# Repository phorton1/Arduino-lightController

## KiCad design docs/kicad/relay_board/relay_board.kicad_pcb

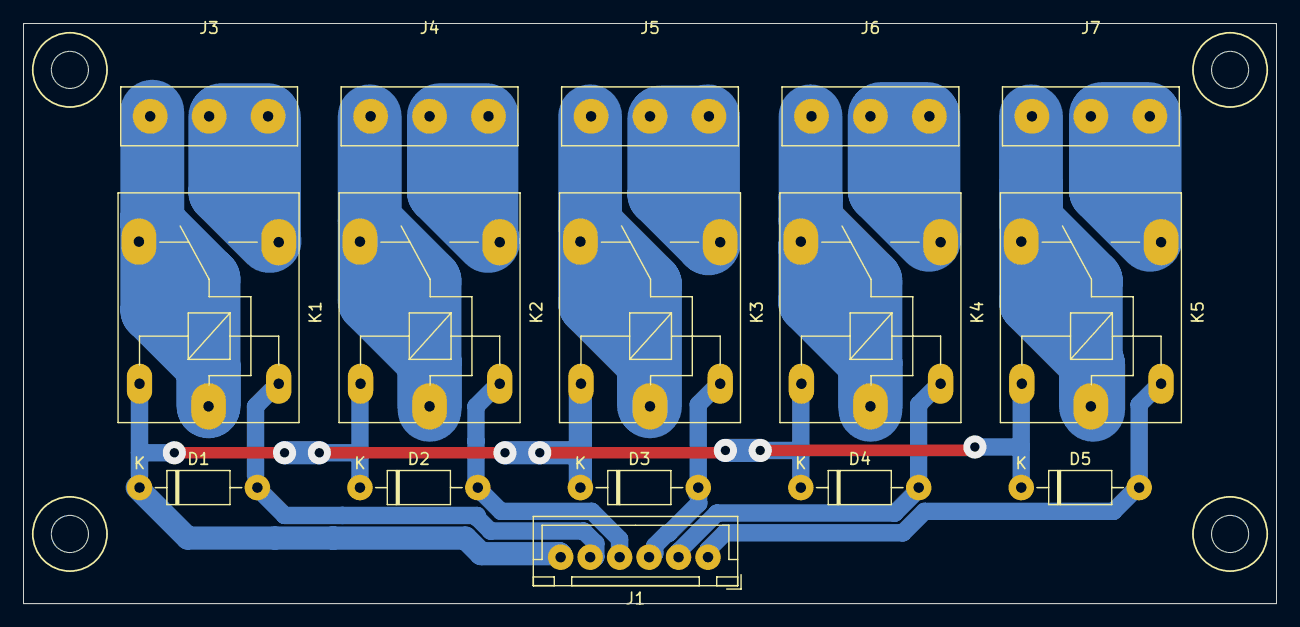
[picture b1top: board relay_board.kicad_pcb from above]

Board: 2 copper layers, 108.0 x 50.0 mm, 16 parts (0 on the bottom side), 16 nets.

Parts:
D1, D2, D3, D4, D5: 1N4001; D_DO-41_SOD81_P10.16mm_Horizontal
J1: RELAYS; myJSTx06
J3: CONN1; Phoenix5.08x3
J4: CONN2; Phoenix5.08x3
J5: CONN3; Phoenix5.08x3
J6: CONN4; Phoenix5.08x3
J7: CONN5; Phoenix5.08x3
K1, K2, K3, K4, K5: myRelay; myRelay2

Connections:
+5V: D1.1, D2.1, D3.1, D4.1, D5.1, J1.6, K1.1, K2.1, K3.1, K4.1, K5.1
unnamed: J3.1, K1.3, K1.4
unnamed: J3.2, J3.3, K1.5
unnamed: J4.1, K2.3, K2.4
unnamed: J4.2, J4.3, K2.5
unnamed: J5.1, K3.3, K3.4
unnamed: J5.2, J5.3, K3.5
unnamed: J6.1, K4.3, K4.4
unnamed: J6.2, J6.3, K4.5
unnamed: J7.1, K5.3, K5.4
unnamed: J7.2, J7.3, K5.5
RELAY1: D1.2, J1.5, K1.2
RELAY2: D2.2, J1.4, K2.2
RELAY3: D3.2, J1.3, K3.2
RELAY4: D4.2, J1.2, K4.2
RELAY5: D5.2, J1.1, K5.2

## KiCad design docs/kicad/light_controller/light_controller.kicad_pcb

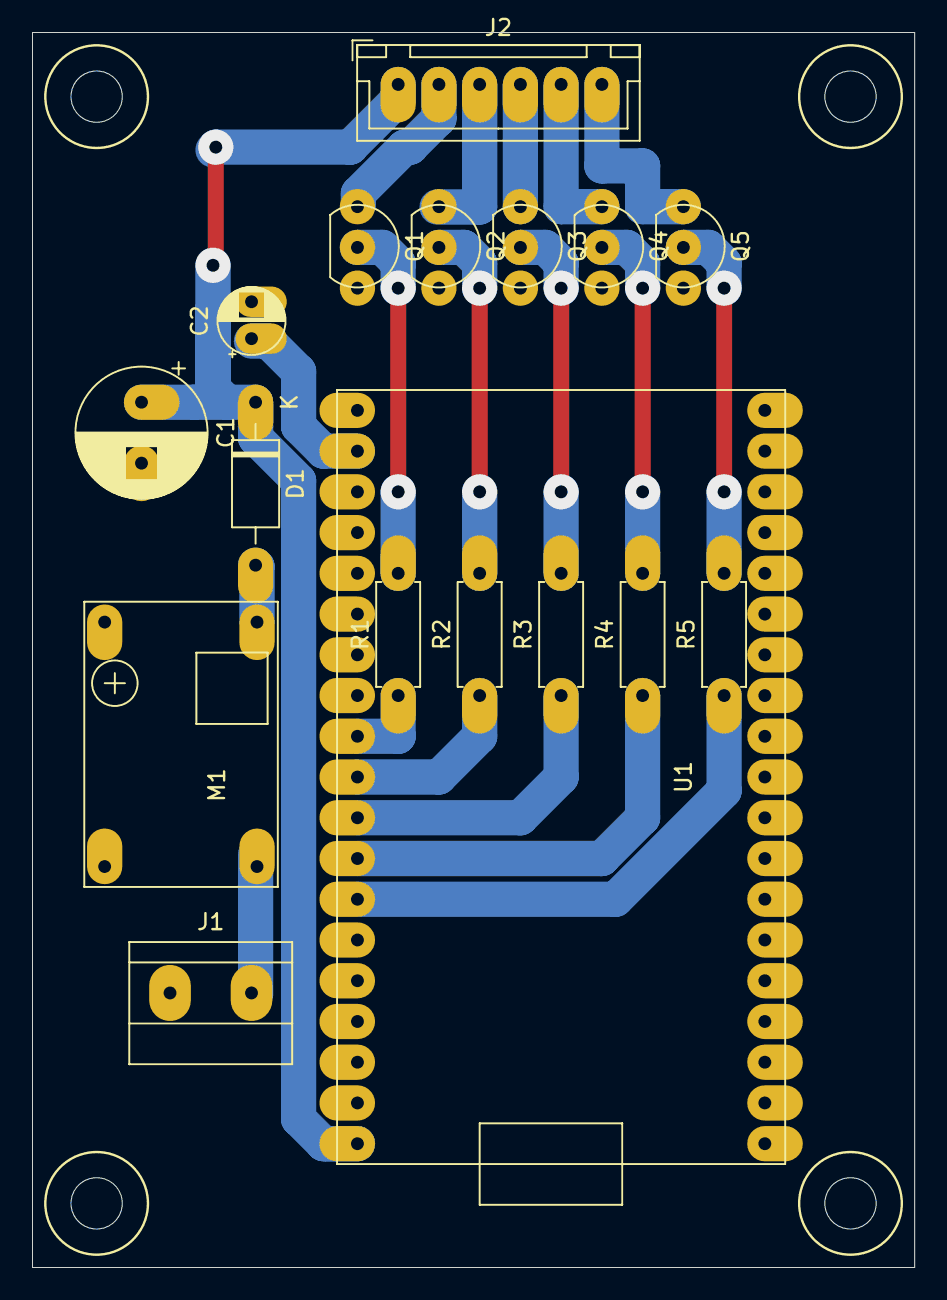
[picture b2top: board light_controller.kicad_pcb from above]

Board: 2 copper layers, 55.0 x 77.0 mm, 17 parts (0 on the bottom side), 20 nets.

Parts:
C1: 100uf; CP_my100uf
C2: 4.7uf; CP_my10uf
D1: 1N4001; D_DO-41_SOD81_P10.16mm_Horizontal
J1: POWER; myTerminalBlock_5.08x02
J2: Conn_01x06; myJSTx06
M1: BUCK01; buck-mini360
Q1, Q2, Q3, Q4, Q5: BC549; myTransistor
R1, R2, R3, R4, R5: 1K; resistor
U1: ESP32_DEV; esp32_dev

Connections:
+5V: C1.1, D1.1, J2.1, U1.1
CONTROL1: R1.1, U1.11
CONTROL2: R2.1, U1.10
CONTROL3: R3.1, U1.9
CONTROL4: R4.1, U1.8
CONTROL5: R5.1, U1.7
GND: C1.2, C2.2, J1.1, M1.1, M1.2, Q1.3, Q2.3, Q3.3, Q4.3, Q5.3, U1.6, U1.20, U1.26
unnamed: C2.1, U1.18
unnamed: D1.2, M1.3
unnamed: J1.2, M1.4
unnamed: Q1.2, R1.2
unnamed: Q2.2, R2.2
unnamed: Q3.2, R3.2
unnamed: Q4.2, R4.2
unnamed: Q5.2, R5.2
RELAY1: J2.2, Q1.1
RELAY2: J2.3, Q2.1
RELAY3: J2.4, Q3.1
RELAY4: J2.5, Q4.1
RELAY5: J2.6, Q5.1

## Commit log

2025-07-01 added Arduino-lightController repo
2025-07-10 Create relay and light controller PCB's; test
2025-07-29 added potential water level monitoring schematic to light controller
2025-12-15 submodule(data) auto_commit(b649fc3a) iotChart.js - added scheme for setting device specific series colors
2025-12-18 submodule(data) auto_commit(1adaeb45) reworked iotChart.js incremental update scheme starting with Arduino-boat-drainPump
2025-12-18 submodule(data) auto_commit(b6ac0c88) starting in Arduino-boat-arirco, major rework of iotChart.js and how charts are implemented - use common chart.html instead of specific/extra_data/device_chart.h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
2025-12-18 submodule(data) auto_commit(1efc7b72) rework iotChart.js::determineNumberTicks() starting with drain_pump
2025-12-18 submodule(data) auto_commit(78894e93) change onChartResize() to use create_chart() instead of built in jqplot.replot()
2025-12-18 submodule(data) auto_commit(40916b0c) separate iotChart.js doChart() as init only method from onXXX() UI methods - yet another rework of iotChart.js and myIOTDataLog starting with fridgeController
2025-12-18 submodule(data) auto_commit(b923e44d) back to static html for chart.html; got rid of myIOTDataLog::getChartHtml() starting with tempController
2025-12-18 submodule(data) auto_commit(a4e2ed81) change chart.html and iotChart.js to use and remove style "degree_hidden" for devices that chart things with degrees
2025-12-18 submodule(data) auto_commit(a9754dbc) fixed renamed control _degree_type
2025-12-18 submodule(data) auto_commit(03555741) fix malformed chart.html <select id='_chart_period'> text
2025-12-19 submodule(data) auto_commit(1cb3d61a) add onChartResize() back to chart.html
2025-12-19 submodule(data) auto_commit(253976a9) more changes to iotChart.js starting with tempController so at least refresh works *well* if no zooming involved
2025-12-19 commit parents
2025-12-20 submodule(data) auto_commit(eccd1fcc) iotChart.js - added save/restore of series visibility and refactored code
2025-12-31 submodule(data) auto_commit(2a8db875) add degree_type to myIOT chart_header for use in initializing iotChart.js
2026-02-22 submodule(data) auto_commit(37a6a76c) added framework for chart.html to pass "data_name" to allow multiple charts per device; ALSO store most recent chart period in browser storage
2026-03-04 submodule(data) auto_commit(75bcbcb5) iotChart.js - added smaller (UINT8, CENTIGRADE8, UINT8x10) iotDataLog LOG_TYPES and updated client ctors
2026-03-04 submodule(data) auto_commit(d6f02205) added myIotTempSensor "raw" accessors & used to shrink fridgeController.dataLog file size; got rid of FAKE_COMPRESSOR
2026-03-05 added "boat" to the myIOTDevice advertised SSDP device URL
2026-03-05 submodule(data) auto_commit(ecc76888) update myIOT data submodule readme.md to remove forward references to actual implmented device repos
2026-03-07 submodule(data) auto_commit(5dbe3136) Save chart visibility and zorders in locsl storage
2026-04-04 submodule(data) auto_commit(a0279fca) New iotChart tooltips and dataLog record maintenance feature.
2026-04-04 submodule(data) auto_commit(de0689cf) disable Scan/Delete endpoints and just View data records for devices that have graphs, but no SD card
2026-06-28 submodule(data) auto_commit(eadab9ea) added myIOTDataLog type LOG_COL_TYPE_INT16_10 to support volts (fridgeController)
